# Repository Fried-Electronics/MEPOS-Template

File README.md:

# MEPOS-Template
Modular Electronics Prototyping Obviously Stackable.

This is where it all begins, a template for all other modules built on the MEPOS architecture.

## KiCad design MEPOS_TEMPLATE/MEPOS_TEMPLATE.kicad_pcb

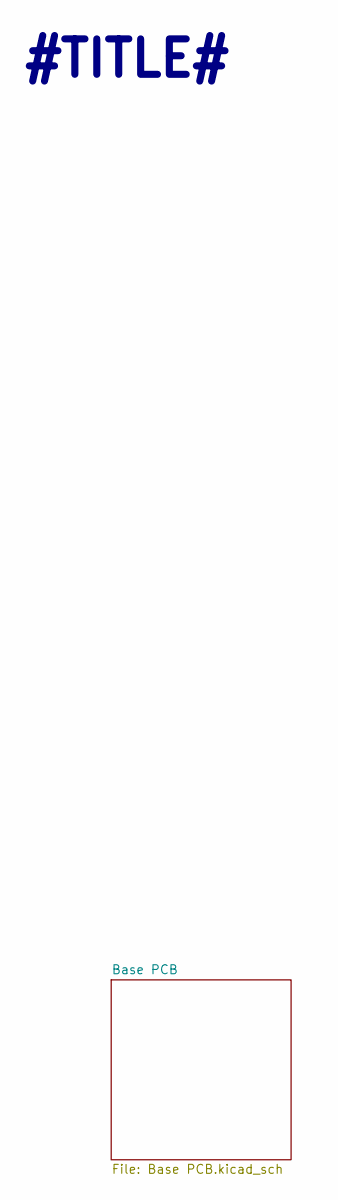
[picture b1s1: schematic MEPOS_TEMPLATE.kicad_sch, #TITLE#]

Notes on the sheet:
#TITLE#

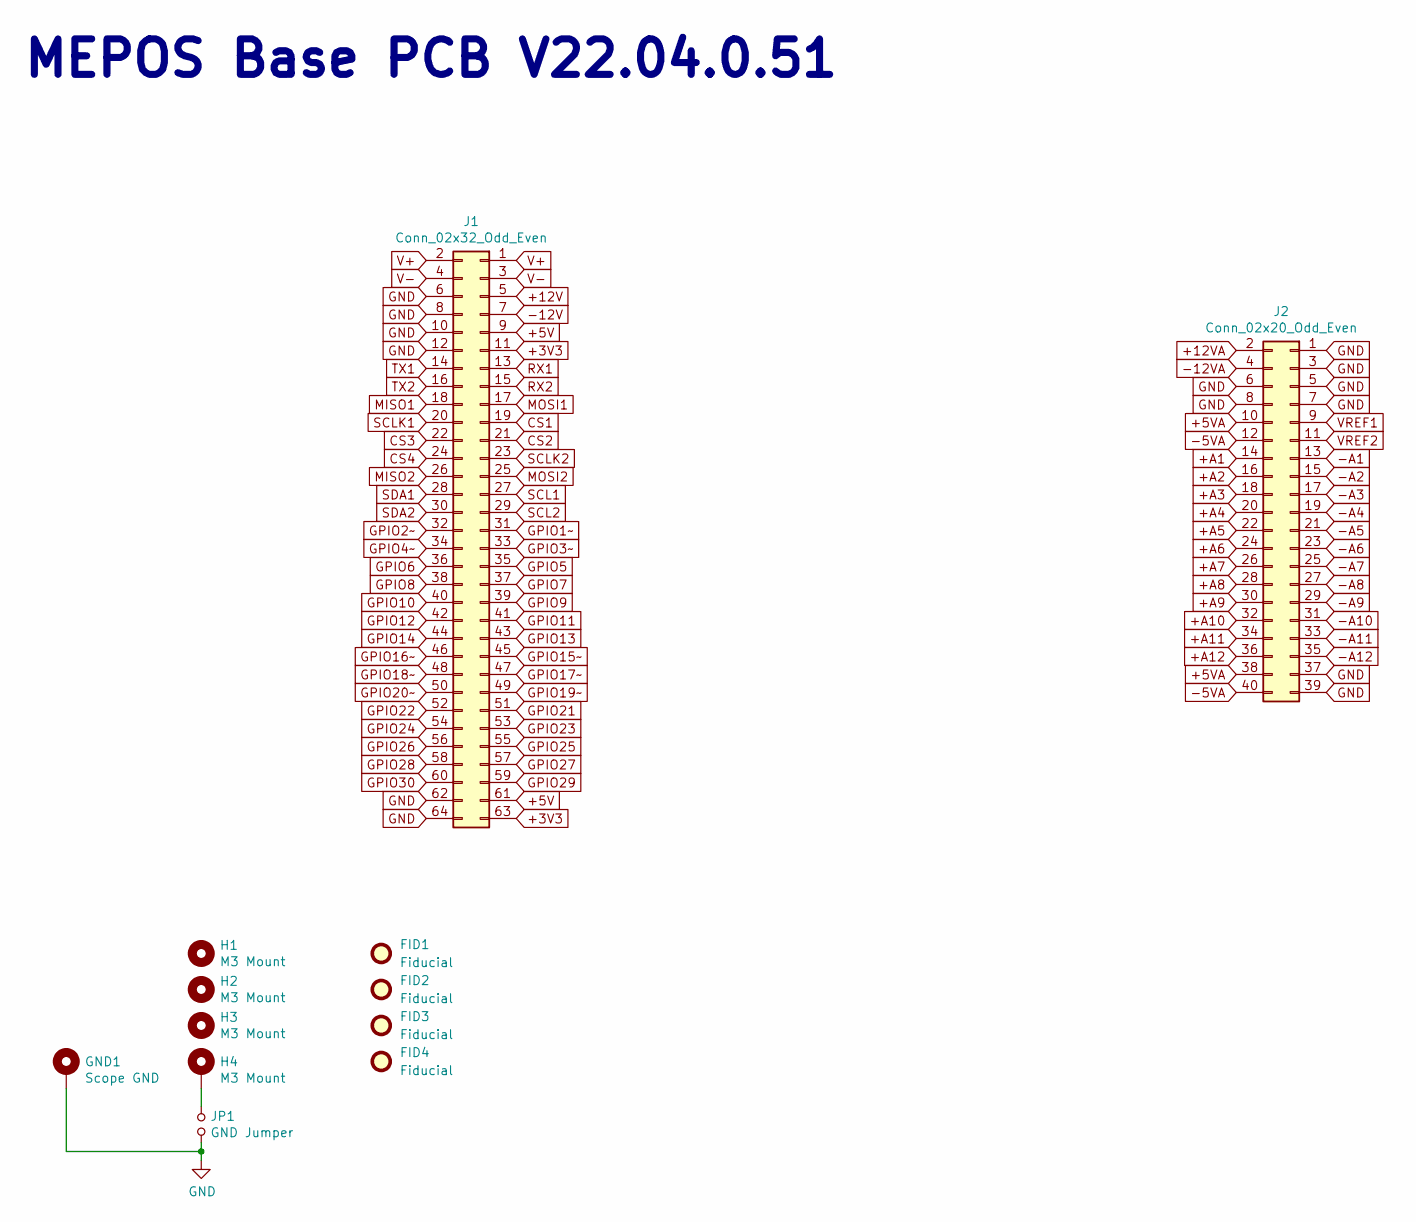
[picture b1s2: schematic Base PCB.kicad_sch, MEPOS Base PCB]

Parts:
FID1, FID2, FID3, FID4: Fiducial; Fiducial_0.75mm_Mask1.5mm
GND1: Scope GND; Scope_GND
H1, H2, H3, H4: M3 Mount; MountingHole_3.2mm_M3_Pad
J1: Conn_02x32_Odd_Even; PinSocket_2x32_P2.54mm_Vertical
J2: Conn_02x20_Odd_Even; PinSocket_2x20_P2.54mm_Vertical
JP1: GND Jumper; TestPoint_2Pads_Pitch2.54mm_Drill0.8mm

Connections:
+3V3: J1.11, J1.63
+5V: J1.9, J1.61
+5VA: J2.10, J2.38
+12V: J1.5
+12VA: J2.2
+A1: J2.14
+A2: J2.16
+A3: J2.18
+A4: J2.20
+A5: J2.22
+A6: J2.24
+A7: J2.26
+A8: J2.28
+A9: J2.30
+A10: J2.32
+A11: J2.34
+A12: J2.36
-5VA: J2.12, J2.40
-12V: J1.7
-12VA: J2.4
-A1: J2.13
-A2: J2.15
-A3: J2.17
-A4: J2.19
-A5: J2.21
-A6: J2.23
-A7: J2.25
-A8: J2.27
-A9: J2.29
-A10: J2.31
-A11: J2.33
-A12: J2.35
CS1: J1.19
CS2: J1.21
CS3: J1.22
CS4: J1.24
GND: GND1.1, J1.6, J1.8, J1.10, J1.12, J1.62, J1.64, J2.1, J2.3, J2.5, J2.6, J2.7, J2.8, J2.37, J2.39, JP1.2
GPIO1~: J1.31
GPIO2~: J1.32
GPIO3~: J1.33
GPIO4~: J1.34
GPIO5: J1.35
GPIO6: J1.36
GPIO7: J1.37
GPIO8: J1.38
GPIO9: J1.39
GPIO10: J1.40
GPIO11: J1.41
GPIO12: J1.42
GPIO13: J1.43
GPIO14: J1.44
GPIO15~: J1.45
GPIO16~: J1.46
GPIO17~: J1.47
GPIO18~: J1.48
GPIO19~: J1.49
GPIO20~: J1.50
GPIO21: J1.51
GPIO22: J1.52
GPIO23: J1.53
GPIO24: J1.54
GPIO25: J1.55
GPIO26: J1.56
GPIO27: J1.57
GPIO28: J1.58
GPIO29: J1.59
GPIO30: J1.60
MISO1: J1.18
MISO2: J1.26
MOSI1: J1.17
MOSI2: J1.25
unnamed: H4.1, JP1.1
RX1: J1.13
RX2: J1.15
SCL1: J1.27
SCL2: J1.29
SCLK1: J1.20
SCLK2: J1.23
SDA1: J1.28
SDA2: J1.30
TX1: J1.14
TX2: J1.16
V+: J1.1, J1.2
V-: J1.3, J1.4
VREF1: J2.9
VREF2: J2.11

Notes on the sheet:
MEPOS Base PCB V22.04.0.51

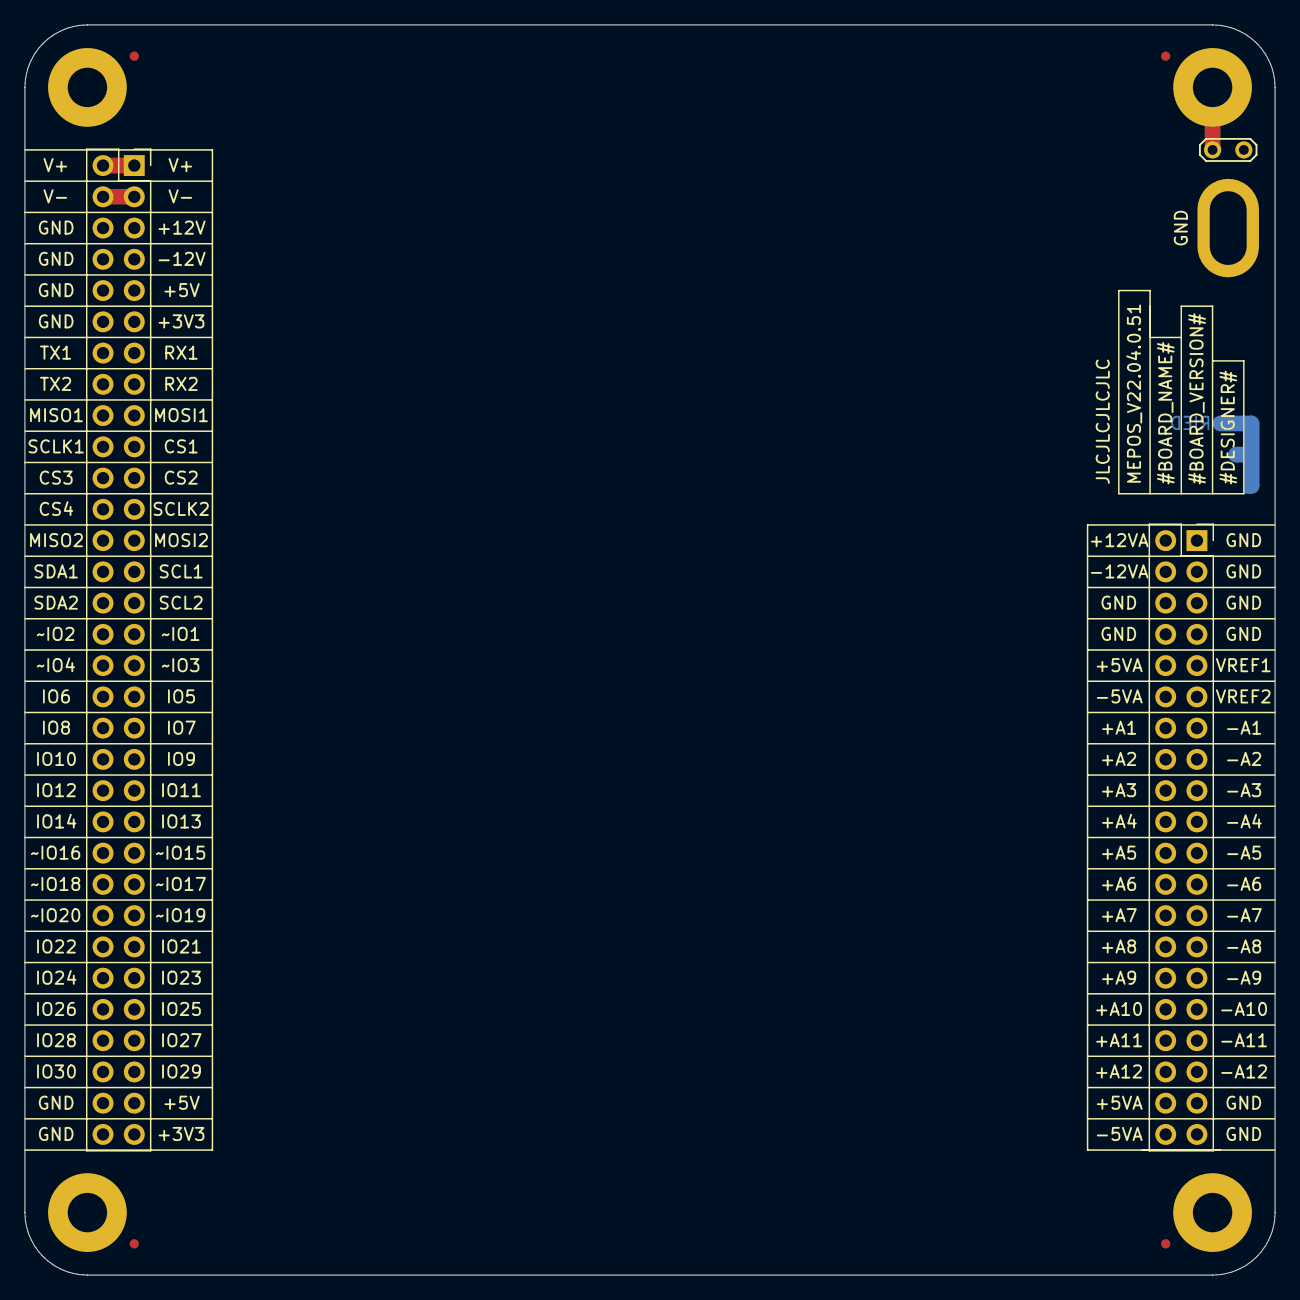
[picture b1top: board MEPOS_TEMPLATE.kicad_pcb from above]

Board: 4 copper layers, 101.6 x 101.6 mm, 13 parts (1 on the bottom side), 8 nets.

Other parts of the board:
KiCad_Logo: KiCad-Logo2_5mm_SilkScreen

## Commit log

2022-05-15 Updated to MEPOS V0.5
    -updated pinout so pin names matched schematic.
    -added paste holes for alignment
2022-05-23 Updated Silkscreen version error
2022-05-23 Add front and back to drawing layer
2022-06-08 Changed logo to a footprint so that it can be used on other projects
2022-06-08 Updated Libraries
2022-06-08 Update MEPOS_TEMPLATE.kicad_pcb
    Lock logo footprint
2022-07-11 Added Icon to footprints and changed design rules to JLCPCBs rules
2022-07-12 Added Origins
    Added origins for drill and place files at bottom left hand side of board
2022-07-26 Updated copper to edge clearance
2022-07-26 Updated DRC error and removed edge silkscreen
2022-07-28 Updated to MEPOS V22.07.0.51
    Added fiducial markers to the topside of the board
2022-07-29 Deleted extra backup files
